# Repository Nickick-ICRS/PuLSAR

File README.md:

# PuLSAR - Probabilistic Localisation of SwArm Robots

ME4 Master's Project of Nick Hafner

Supervised by Dr Ravi Vaidyanathan

Imperial College London Department of Mechanical Engineering

## Overview of repository

This repository contains the code to localise a swarm of PuLSARs. The code is research code and no liability can be taken for any losses owing to the direct or indirect usage of this code.

The repository also contains CAD files for the Kicad PCB and Solidworks models.

## Example Usage

First follow the installation instructions below.

### Running Gazebo
(In a new terminal)
To launch a Gazebo-simulated swarm of 20 robots with the Group Motion state machine:

`$ roslaunch pulsar_gazebo multiple_robots.launch num_robots:=20 state_machine_type:=group_target`.

To launch a Gazebo-simulated swarm of 10 robots with no state machine running:

`$ roslaunch pulsar_gazebo multiple_robots.launch num_robots:=10 run_state_machine:=false`

### Running Localisation Algorithms
(With Gazebo running, in a new terminal)
To launch PSOSwarmPoseEstimator with a swarm of 20 robots:

`$ roslaunch pulsar_localisation localisation.launch num_robots:=20 localiser:=pso robot_model:=scan_matching`.

To launch AverageMCLSwarmPoseEstimator with a swarm of 10 robots and the odometry robot model:

`$ roslaunch pulsar_localisation localisation.launch num_robots:=10 localiser:=average_swarm_mcl robot_model:=odometry`.

To launch MCLSwarmPoseEstimator with a swarm of 5 robots and the scan matching robot model, debugging using Valgrind//KCacheGrind:

`$roslaunch pulsar_localisation localisation.launch num_robots:=5 localiser:=mcl robot_model:=scan_matching valgrind:=true`.

etc...

### Changing Algorithm Parameters

Edit pulsar_localisation's `localisation.launch` file. See the package README or file comments for details on what parameters do.

## Requirements

### Building

This repository used [Catkin](wiki.ros.org/catkin) to build the sub-components. This is installed along with ROS - this set of packages has been written to run with [ROS Melodic](http://wiki.ros.org/melodic/Installation) on **Ubuntu 18.04** with **Bash**. Please start by installing ROS Melodic before attempting to install any of these packages.

Create the following directory layout:
```
catkin_ws
  -> src
```

Run

`cd catkin_ws/src && catkin_init_workspace && cd .. && catkin_make` 

to generate the initial workspace. After this, clone this repository into the src folder:

`cd src && git clone <this package url>`

Install the required dependencies:

`cd PuLSAR && ./install_dependencies.sh`

Finally build the full set of packages:

`cd ../.. && catkin_make`

## Package Layout

### pulsar_cad

This package contains the CAD files needed to manufacture the PuLSAR robots. Solidworks and Kicad were used for mechanical and electrical design respectively. Kicad is free, however Solidworks will require a license to view files.

### pulsar_description

This package contains the stl meshes and urdf files required for the robot description in the ROS ecosystem. URDF has been split up into multiple files, with `urdf/pulsar.urdf.xacro` the top level URDF file.

### pulsar_gazebo

This package contains files relevant to simulating PuLSAR in the Gazebo robot simulator.

#### Launch

The launch folder contains the roslaunch files necessary to launch the simulation environment. `one_robot.launch` launches a single robot, while `multiple_robots.launch` will spawn multiple robots.

##### One Robot

This launch file spawns one pulsar robot with accompanying nodes (not localisation) in the Gazebo simulator, optionally starting the simulator. It is supposed to be called recursively from `multiple_robots.launch`, but exposes the following parameters if a user wishes to use it:

- robot_ns - The name(space) of the robot. String. Default is 'pulsar_0'.
- launch_gazebo - Whether to launch gazebo or not. Boolean. Default is true.
- start_x - The starting x position of the robot. Decimal. Default is 0.
- start_y - The starting y position of the robot. Decimal. Default is 0.
- start_yaw - The starting yaw position of the robot in radians. Decimal. Default is 0.
- start_z - The starting z height of the robot. Useful for preventing robots from clipping through the floor. Decimal. Default is 0.02.
- run_state_machine - Should the launch file spawn a state machine for the robot. Boolean. Default is true.
- state_machine_type - Which state machine should be spawned (see pulsar_state_machines). String. Default is "default". Options are:
    - "default" - Random movement state machine.
    - "group_target" - State machine which attempts to group with other robots and move towards a target point.
- map_file - Which map file to use. String. Default is "\<location of pulsar_gazebo>/maps/map.yaml".

##### Multiple Robots

This launch file spawns a swarm of pulsar robots in the Gazebo simulator, and starts the simulator. The robots are spawned in random (valid) positions. It exposes the following parameters:

- num_robots - The numberof robots to spawn. Integer. Default is 5.
- run_state_machine - Should the launch file spawn a state machine for the robot. Boolean. Default is true.
- state_machine_type - Which state machine should be spawned (see pulsar_state_machines). String. Default is "default". Options are:
    - "default" - Random movement state machine.
    - "group_target" - State machine which attempts to group with other robots and move towards a target point.
- map_file - Which map file to use. String. Default is "\<location of pulsar_gazebo>/maps/map.yaml".

### pulsar_hardware

Contains code to be compiled for the ESP-32 on the robots. Note that due to the impacts of COVID-19 on the university and project, robots could not be tested. As such this package is unfinished and has been included for completion.

### pulsar_lib

Contains custom libraries used both in simulation and in hardware such as EKF, PI controllers and Odometry.

### pulsar_localisation

Contains the developed localisation algorithms and surrounding infrastructure. It also contains the localisation launch file.

#### Launch

The launch file will run one of the localisation algorithms developed as part of this project. This should only be launched once all the robots have successfully been loaded into Gazebo. It has the following command line parameters:
- num_robots - The number of robots to localise. Should match the multiple robots launchfile parameter of the same name. Integer. Default is 1.
- valgrind - Allows the node to be launched under Valgrind for intensive debugging (e.g. function call counts). Takes precedence over gdb. Boolean. Default is false.
- gdb - Allows the node to be launched in gdb for debugging with breakpoints etc. Boolean. Default is false.
- localiser - Which localisation algorithm to use. String. Default is "mcl". Options are:
    - mcl - Runs the MCLSwarmPoseEstimator algorithm.
    - average_swarm_mcl - Runs the AverageMCLSwarmPoseEstimator algorithm. This algorithm was found to perform best.
    - pso - Runs the PSOSwarmPoseEstimator algorithm.
- robot_model - Picks which robot model to use. Note that PSO only supports scan_matching. String. Default is "odometry". Options are:
    - odometry - The odometry motion model (variant of Thrun et al.'s (2010) **odometry_motion_model**). Found to perform best.
    - scan_matching - The scan matching model.

For finer details on this launch file see the pulsar_localisation README.

### pulsar_server

Contains code to connect to robots via TCP, effectively the bridge between ROS and individual robots. Unfinished due to COVID-19, but included for completion.

### pulsar_state_machines

Contains robot state machines for swarm movement. Two state machines exist:
- Random Movement - move randomly
- Group Movement - form a group and move to a target

#### Node

The `state_machine` node runs a state machine for a given robot. It takes the following parameters:
- state_machine - Which state machine to use. String. Default is "default". Options are:
    - default - The default, random movement state machine.
    - group_target - The group motion state machine.
- robot_ns - The robot name(space). String. Default is "pulsar_0".
- update_freq - The state machine update frequency in Hz. Decimal. Default is 10.
- delay - Delay the start of state machine logic in seconds. Decimal. Default is 0.

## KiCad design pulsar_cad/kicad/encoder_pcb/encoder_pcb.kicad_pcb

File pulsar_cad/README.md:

# pulsar_cad

This package contains the CAD files needed to manufacture the PuLSAR robots.

## Kicad

The files within this folder are board layouts for the different PCBs designed using Kicad. There are three boards:
- Encoder - Contains the AS5047P magnetic encoders. 1 required per robot.
- Main Body - Contains the main components (motor driver, ESP-32, IMU etc.). 1 required per robot.
- Range Finders - Contains the VL53L0X range sensor. 3 required per robot.

## Solidworks

TODO: description of solidworks files.

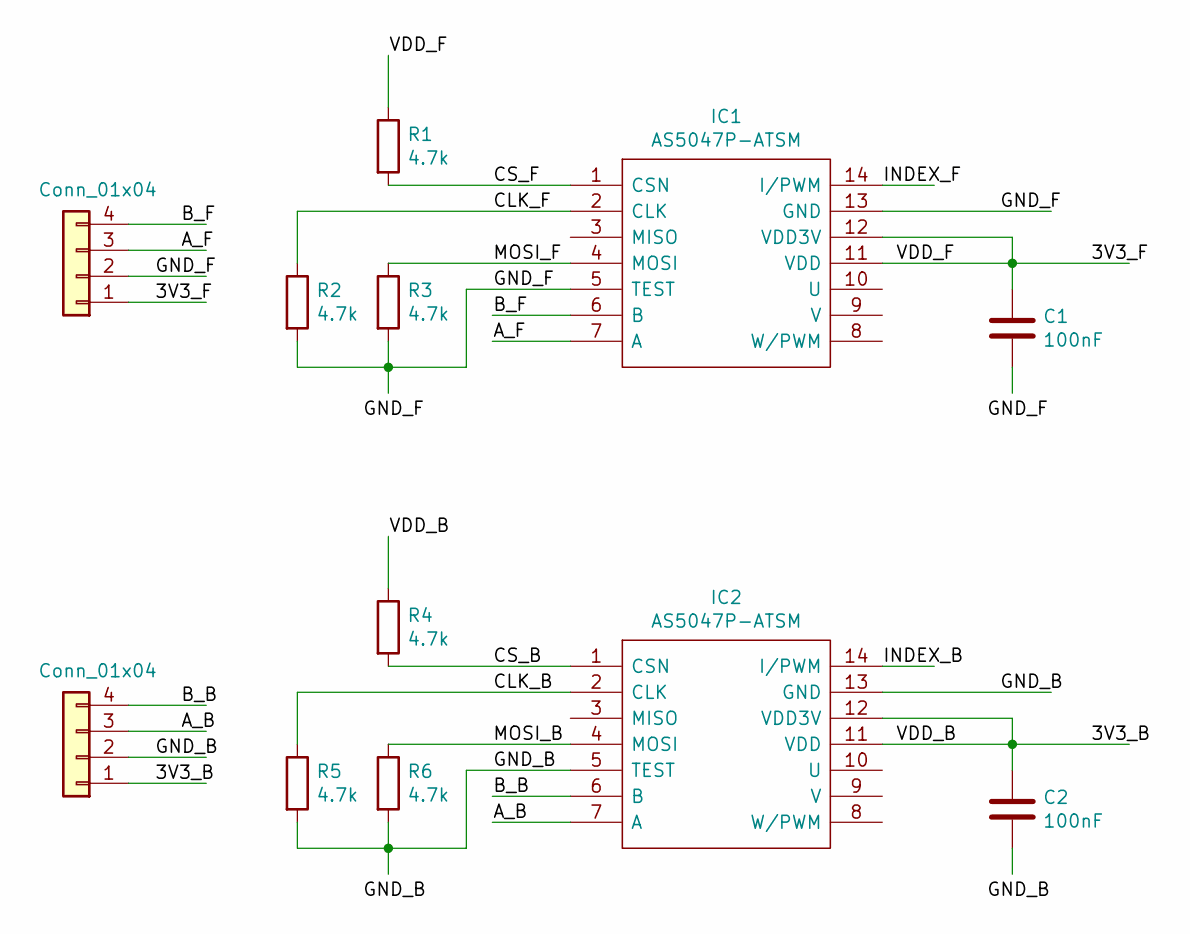
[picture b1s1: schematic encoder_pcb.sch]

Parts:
C1, C2: 100nF; C_0805_2012Metric
IC1, IC2: AS5047P-ATSM; SOP65P640X120-14N; Manufacturer_Part_Number AS5047P-ATSM
J1, J2: Conn_01x04; Connector_Pad_4x2.0x2.0mm
R1, R2, R3, R4, R5, R6: 4.7k; R_0805_2012Metric

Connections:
/3V3_B: C2.1, IC2.11 (VDD), IC2.12 (VDD3V), J2.1, R4.1
/3V3_F: C1.1, IC1.11 (VDD), IC1.12 (VDD3V), J1.1, R1.1
/A_B: IC2.7 (A), J2.3
/A_F: IC1.7 (A), J1.3
/B_B: IC2.6 (B), J2.4
/B_F: IC1.6 (B), J1.4
/CLK_B: IC2.2 (CLK), R5.1
/CLK_F: IC1.2 (CLK), R2.1
/CS_B: IC2.1 (CSN), R4.2
/CS_F: IC1.1 (CSN), R1.2
/GND_B: IC2.5 (TEST), IC2.13 (GND), J2.2, R5.2, R6.2
/GND_F: IC1.5 (TEST), IC1.13 (GND), J1.2, R2.2, R3.2
/INDEX_B: IC2.14 (I/PWM)
/INDEX_F: IC1.14 (I/PWM)
/MOSI_B: IC2.4 (MOSI), R6.1
/MOSI_F: IC1.4 (MOSI), R3.1

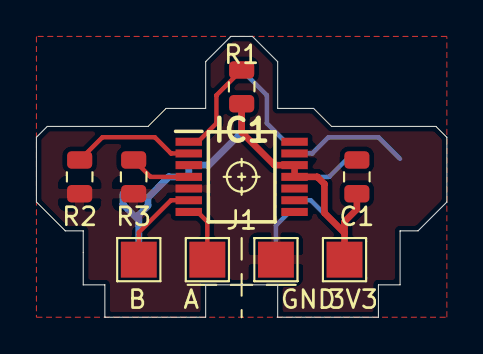
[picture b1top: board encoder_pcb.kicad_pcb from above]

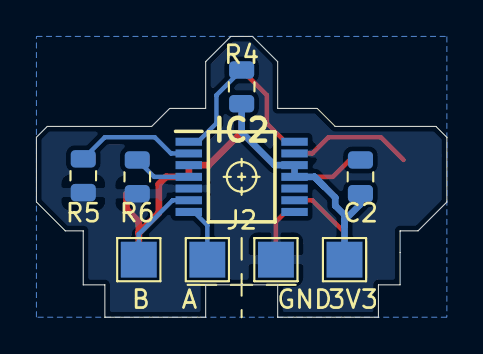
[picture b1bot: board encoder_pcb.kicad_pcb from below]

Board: 2 copper layers, 22.8 x 15.6 mm, 12 parts (6 on the bottom side), 14 nets.

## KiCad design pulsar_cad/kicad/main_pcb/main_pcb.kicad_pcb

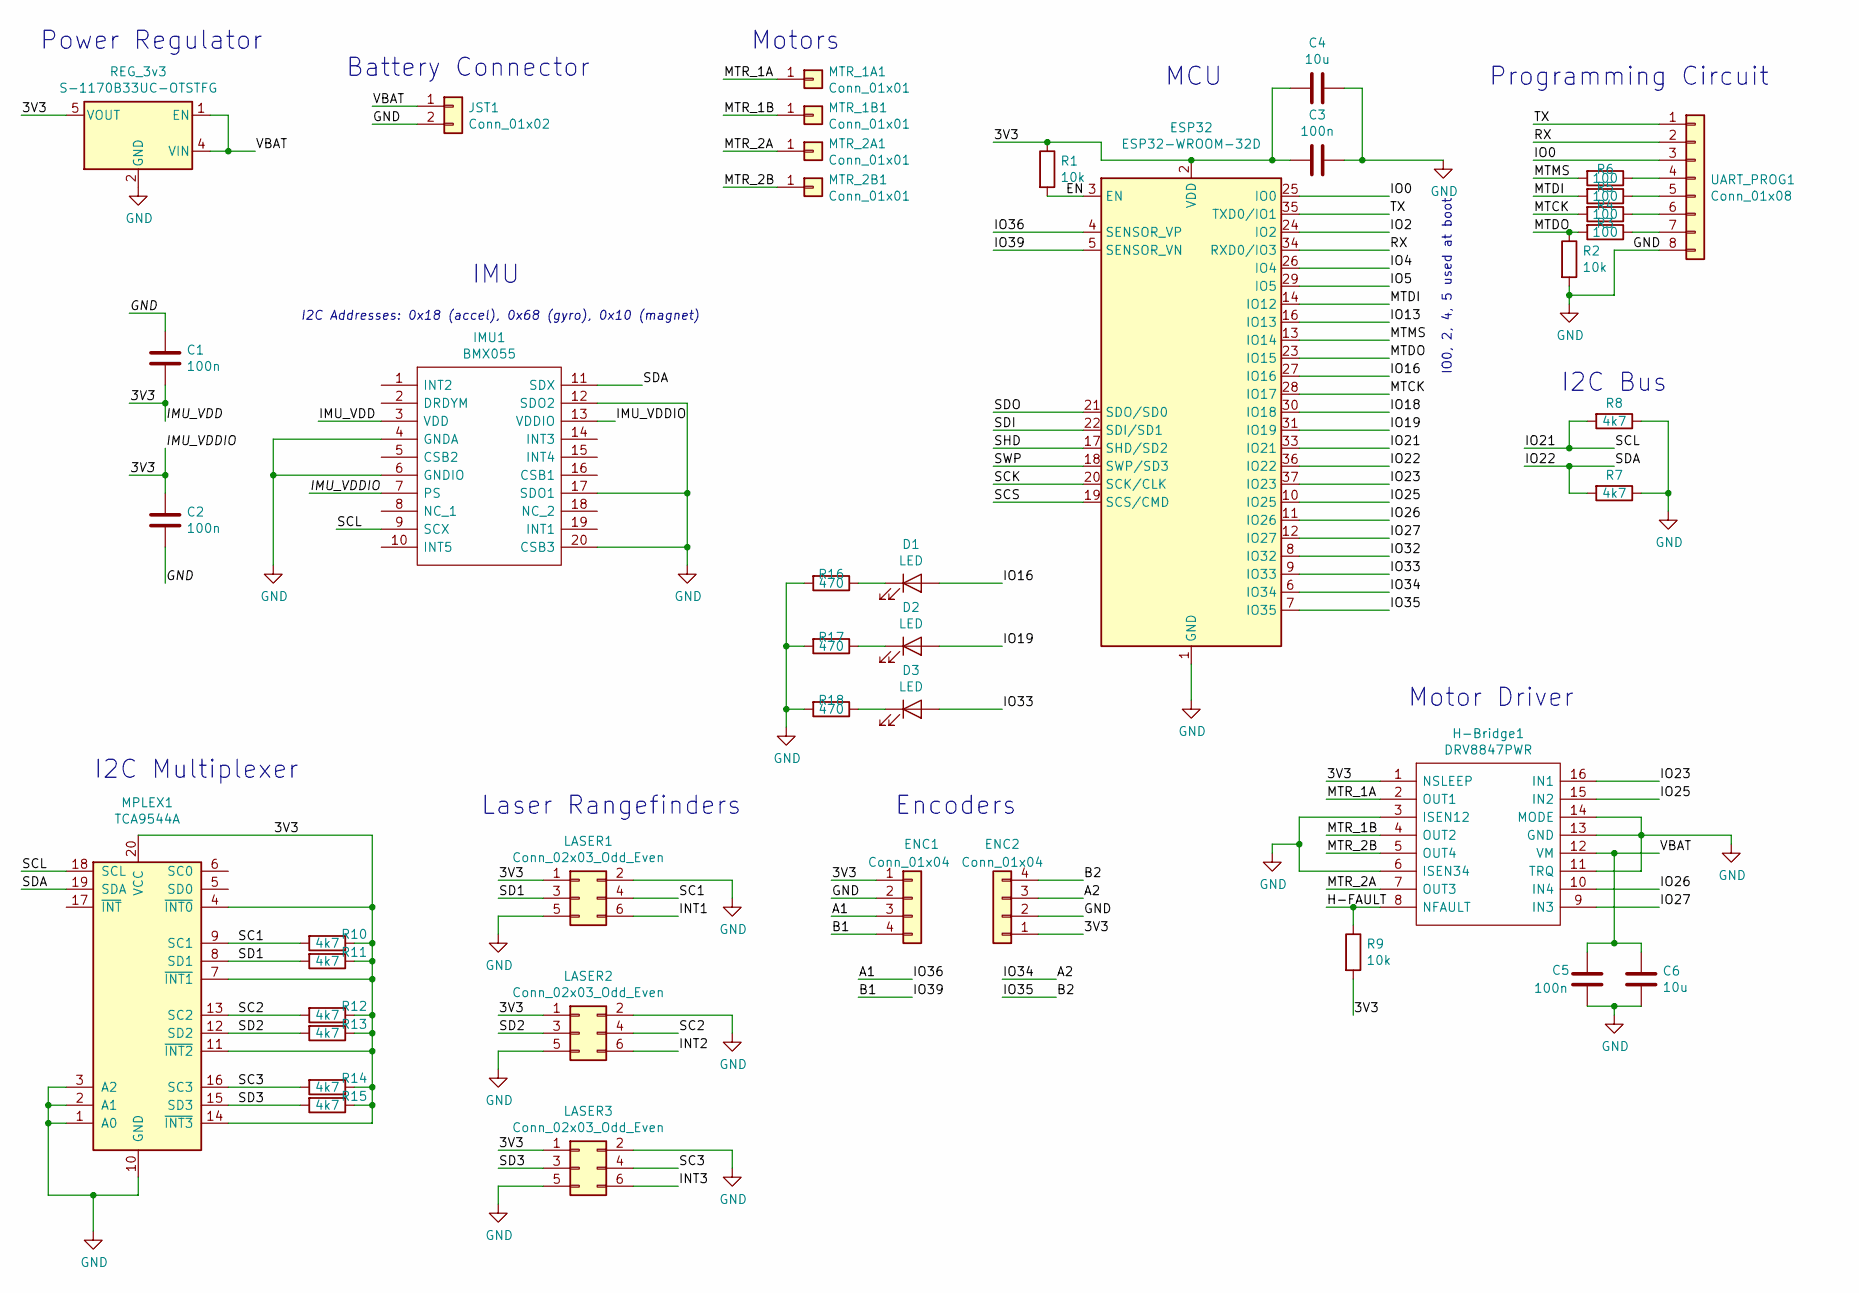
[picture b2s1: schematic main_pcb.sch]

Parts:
C1, C2, C3, C5: 100n; C_0805_2012Metric
C4, C6: 10u; C_0805_2012Metric
D1, D2, D3: LED; D_0805_2012Metric
ENC1, ENC2: Conn_01x04; Connector_Pad_4x2.0x2.0mm
ESP32: ESP32-WROOM-32D; ESP32-WROOM-32
H-Bridge1: DRV8847PWR; SOP65P640X120-16N; Manufacturer_Part_Number DRV8847PWR
IMU1: BMX055; LGA_PACKAGE_20_PINS; Manufacturer_Part_Number BMX055
JST1: Conn_01x02; JST_EH_B2B-EH-A_1x02_P2.50mm_Vertical
LASER1, LASER2, LASER3: Conn_02x03_Odd_Even; PinHeader_2x03_P2.54mm_Horizontal
MPLEX1: TCA9544A; TSSOP-20_4.4x6.5mm_P0.65mm
MTR_1A1, MTR_1B1, MTR_2A1, MTR_2B1: Conn_01x01; PinHeader_1x01_P1.00mm_Vertical
R1, R2, R9: 10k; R_0805_2012Metric
R3, R4, R5, R6: 100; R_0805_2012Metric
R7, R8, R10, R11, R12, R13, R14, R15: 4k7; R_0805_2012Metric
R16, R17, R18: 470; R_0805_2012Metric
REG_3v3: S-1170B33UC-OTSTFG; SOT-89-5
UART_PROG1: Conn_01x08; PinHeader_1x08_P2.54mm_Vertical

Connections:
/3V3: C1.2, C2.1, C3.2, C4.2, ENC1.1, ENC2.1, ESP32.2 (VDD), H-Bridge1.1 (NSLEEP), IMU1.3 (VDD), IMU1.7 (PS), IMU1.13 (VDDIO), LASER1.1, LASER2.1, LASER3.1, MPLEX1.4 (~INT0), MPLEX1.7 (~INT1), MPLEX1.11 (~INT2), MPLEX1.14 (~INT3), MPLEX1.20 (VCC), R1.1, R9.2, R10.1, R11.1, R12.1, R13.1, R14.1, R15.1, REG_3v3.5 (VOUT)
/A1: ENC1.3, ESP32.4 (SENSOR_VP)
/A2: ENC2.3, ESP32.6 (IO34)
/B1: ENC1.4, ESP32.5 (SENSOR_VN)
/B2: ENC2.4, ESP32.7 (IO35)
/EN: ESP32.3 (EN), R1.2
/H-FAULT: H-Bridge1.8 (NFAULT), R9.1
/INT1: LASER1.6
/INT2: LASER2.6
/INT3: LASER3.6
/IO0: ESP32.25 (IO0), UART_PROG1.3
/IO2: ESP32.24 (IO2)
/IO4: ESP32.26 (IO4)
/IO5: ESP32.29 (IO5)
/IO13: ESP32.16 (IO13)
/IO16: D1.2 (A), ESP32.27 (IO16)
/IO18: ESP32.30 (IO18)
/IO19: D2.2 (A), ESP32.31 (IO19)
/IO21: ESP32.33 (IO21), IMU1.9 (SCX), MPLEX1.18 (SCL), R8.2
/IO22: ESP32.36 (IO22), IMU1.11 (SDX), MPLEX1.19 (SDA), R7.2
/IO23: ESP32.37 (IO23), H-Bridge1.16 (IN1)
/IO25: ESP32.10 (IO25), H-Bridge1.15 (IN2)
/IO26: ESP32.11 (IO26), H-Bridge1.10 (IN4)
/IO27: ESP32.12 (IO27), H-Bridge1.9 (IN3)
/IO32: ESP32.8 (IO32)
/IO33: D3.2 (A), ESP32.9 (IO33)
/MTCK: ESP32.28 (IO17), R4.2
/MTDI: ESP32.14 (IO12), R5.2
/MTDO: ESP32.23 (IO15), R2.1, R3.2
/MTMS: ESP32.13 (IO14), R6.2
/MTR_1A: H-Bridge1.2 (OUT1), MTR_1A1.1
/MTR_1B: H-Bridge1.4 (OUT2), MTR_1B1.1
/MTR_2A: H-Bridge1.7 (OUT3), MTR_2A1.1
/MTR_2B: H-Bridge1.5 (OUT4), MTR_2B1.1
/RX: ESP32.34 (RXD0/IO3), UART_PROG1.2
/SC1: LASER1.4, MPLEX1.9 (SC1), R10.2
/SC2: LASER2.4, MPLEX1.13 (SC2), R12.2
/SC3: LASER3.4, MPLEX1.16 (SC3), R14.2
/SCK: ESP32.20 (SCK/CLK)
/SCS: ESP32.19 (SCS/CMD)
/SD1: LASER1.3, MPLEX1.8 (SD1), R11.2
/SD2: LASER2.3, MPLEX1.12 (SD2), R13.2
/SD3: LASER3.3, MPLEX1.15 (SD3), R15.2
/SDI: ESP32.22 (SDI/SD1)
/SDO: ESP32.21 (SDO/SD0)
/SHD: ESP32.17 (SHD/SD2)
/SWP: ESP32.18 (SWP/SD3)
/TX: ESP32.35 (TXD0/IO1), UART_PROG1.1
/VBAT: C5.1, C6.1, H-Bridge1.12 (VM), JST1.1, REG_3v3.1 (EN), REG_3v3.4 (VIN)
GND: C1.1, C2.2, C3.1, C4.1, C5.2, C6.2, ENC1.2, ENC2.2, ESP32.1 (GND), ESP32.15 (GND), ESP32.38 (GND), H-Bridge1.3 (ISEN12), H-Bridge1.6 (ISEN34), H-Bridge1.11 (TRQ), H-Bridge1.13 (GND), H-Bridge1.14 (MODE), IMU1.4 (GNDA), IMU1.6 (GNDIO), IMU1.12 (SDO2), IMU1.17 (SDO1), IMU1.20 (CSB3), JST1.2, LASER1.2, LASER1.5, LASER2.2, LASER2.5, LASER3.2, LASER3.5, MPLEX1.1 (A0), MPLEX1.2 (A1), MPLEX1.3 (A2), MPLEX1.10 (GND), R2.2, R7.1, R8.1, R16.2, R17.2, R18.2, REG_3v3.2 (GND), UART_PROG1.8
unnamed: D1.1 (K), R16.1
unnamed: D2.1 (K), R17.1
unnamed: D3.1 (K), R18.1
unnamed: R3.1, UART_PROG1.7
unnamed: R4.1, UART_PROG1.6
unnamed: R5.1, UART_PROG1.5
unnamed: R6.1, UART_PROG1.4

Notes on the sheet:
I2C Addresses: 0x18 (accel), 0x68 (gyro), 0x10 (magnet)
I2C Bus
Programming Circuit
Power Regulator
Battery Connector
Motor Driver
IMU
MCU
Encoders
IO0, 2, 4, 5 used at boot
Laser Rangefinders
I2C Multiplexer
Motors

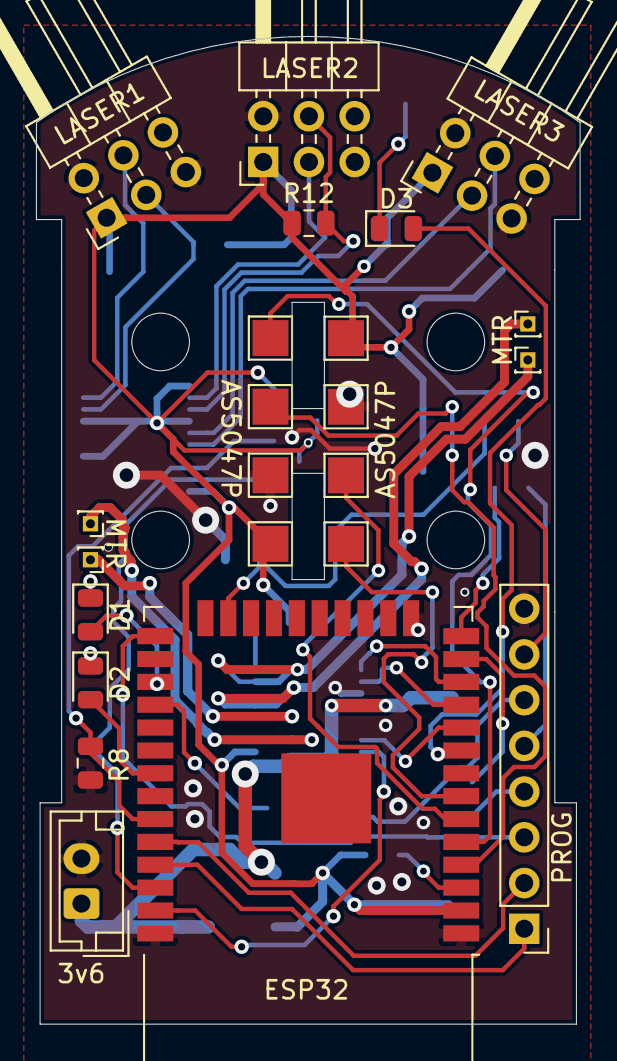
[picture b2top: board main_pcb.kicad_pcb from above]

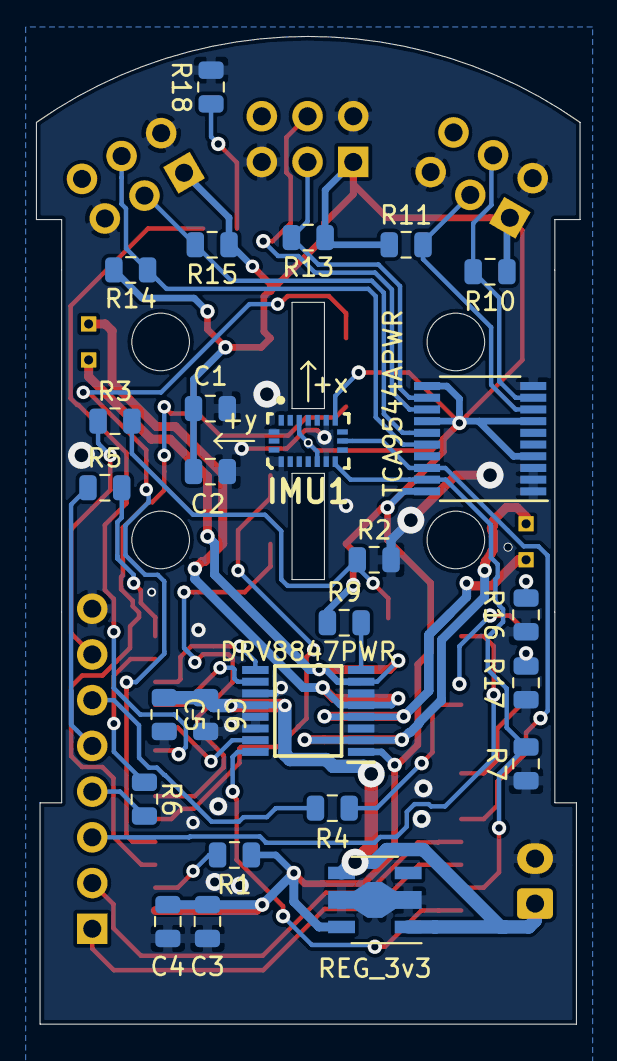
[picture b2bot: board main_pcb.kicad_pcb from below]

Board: 2 copper layers, 30.2 x 54.9 mm, 43 parts (26 on the bottom side), 42 nets.

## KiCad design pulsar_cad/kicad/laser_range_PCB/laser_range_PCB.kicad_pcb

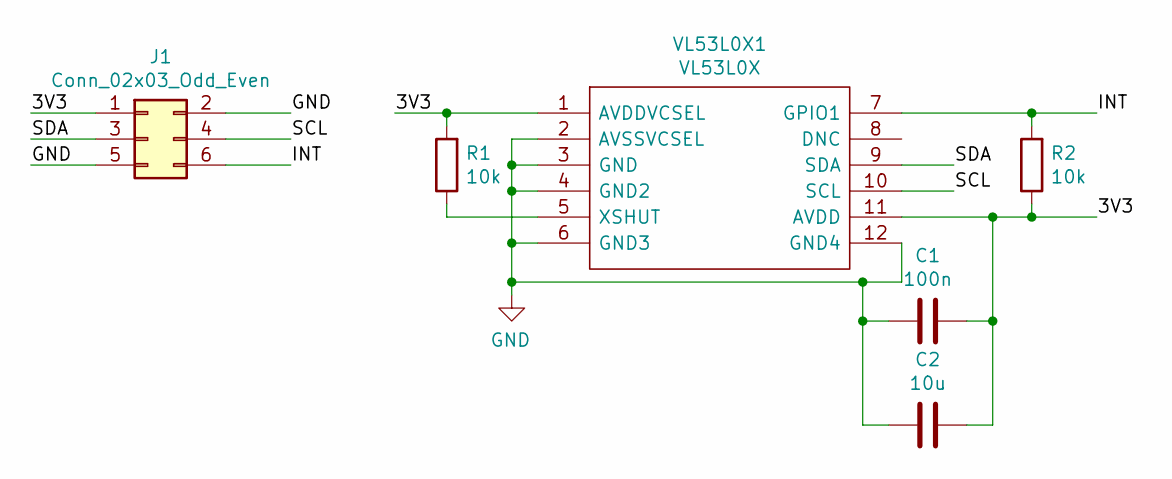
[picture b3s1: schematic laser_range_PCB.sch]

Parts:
C1: 100n; C_0805_2012Metric
C2: 10u; C_0805_2012Metric
J1: Conn_02x03_Odd_Even; PinSocket_2x03_P2.54mm_Vertical
R1, R2: 10k; R_0805_2012Metric
VL53L0X1: VL53L0X; Manufacturer_Part_Number VL53L0X

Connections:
/3V3: C1.1, C2.1, J1.1, R1.2, R2.1, VL53L0X1.1 (AVDDVCSEL), VL53L0X1.11 (AVDD)
/INT: J1.6, R2.2, VL53L0X1.7 (GPIO1)
/SCL: J1.4, VL53L0X1.10 (SCL)
/SDA: J1.3, VL53L0X1.9 (SDA)
GND: C1.2, C2.2, J1.2, J1.5, VL53L0X1.2 (AVSSVCSEL), VL53L0X1.3 (GND), VL53L0X1.4 (GND2), VL53L0X1.6 (GND3), VL53L0X1.12 (GND4)
unnamed: R1.1, VL53L0X1.5 (XSHUT)

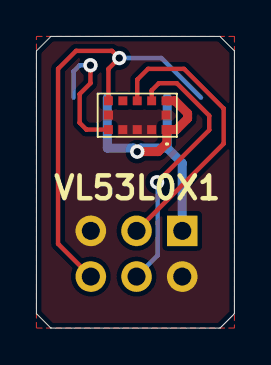
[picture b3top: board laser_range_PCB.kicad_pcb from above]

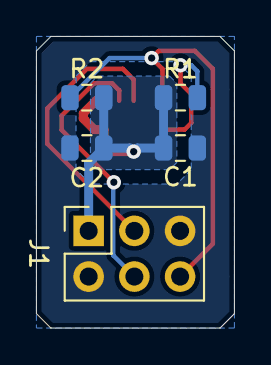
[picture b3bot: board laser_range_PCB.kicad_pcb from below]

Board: 2 copper layers, 11.0 x 16.2 mm, 6 parts (5 on the bottom side), 6 nets.

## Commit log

2019-12-26 Initial commit with a large amount of networking stuff
2020-01-14 Got chassis link loaded correctly into Gazebo, but for some reason the wheel links are missing. This does not appear to be an issue with xacro, in fact the links simply are not coming up in gazebo at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
2020-01-16 Model correctly inserted into gazebo, sensor plugins added.
2020-01-16 Started frameweork on a PuLSAR gazebo plugin to control the robots.
2020-01-19 Created kalman filter library. Successfully compiles but un-tested
2020-01-19 Added odometry library
2020-01-19 Created motor control class. Minor updates to the odometry class
2020-01-19 Moved files around slightly, successfully imported the libraries into the robot plugin
2020-01-20 Corrected submodule requirements and installation script
2020-01-23 Added reverse calculation (i.e. forward kinematics) to odometry class
2020-01-23 Full plugin update cycle is (theoretically) complete and needs testing.
2020-01-23 Added plugin to URDF and briefly checked that it runs in gazebo. Cmd_vel didn't work so some debugging needs to be done.
2020-01-24 Fixed bug with ints instead of floats in odometry
2020-01-24 Successfully got robot moving in simulation. Need to tune PI values before beginning to look at kalman filter results.
2020-02-19 Some progress being made to tuning motor controllers for the simulation - not complete yet however.
2020-02-20 Relatively tuned motor PI controller for simulation
    Kalman filter spits out NaN values so that needs to be fixed next.
2020-02-20 Fixed the Kalman filter issue with NaNs. Kalman filter needs tuning and figuring out why theta is not being used to update the x and y positions
2020-03-02 Big current hardware commit that I should have done in multiple commits quite a while ago
2020-03-05 Fixed bug with odometry, changed physics engine. Played with friction values.
2020-03-08 Implemented ROS EKF to allow algorithm to be developed and custom EKF fixed later. Fixed bug when calculating linear speeds in odometry. There is noticeable drift in simulation (which is good - that'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
2020-03-10 Adjusted one_robot.launch to allow for multiple robots to be launched in different namespaces, in different positions.
2020-03-10 Working launch file for multiple robots in the same simulation
2020-03-10 Removed print statements temporarily as will look at in the future. Fixed an issue in how friction was specified, but this has not changed the turning issue.
2020-03-21 Initial work on creating the cloud of points from robot sensors.
2020-03-21 Fixed bug causing all nodes to shut down once the last robot had been spawned
2020-03-23 Created localisation launch file, added parameters to the localisation node.
2020-03-23 Some mods to range finder coning. Updated world to have walls.
2020-03-24 Updated script to pause gazebo while robots are being spawned in and unpause once robots have all been spawned.
2020-03-24 updated cloud generator to remove old data points.
2020-03-27 Created new pose estimator classes, and rearranged layout slightly. Created parameters for pose estimator classes, next step is to fill in the algorithms.
2020-03-27 Implemented many of the Probabilistic Robotics algorithms in the SingleRobotPoseEstimator. Measurement models not implemented yet. Initial work on the map class, pose validation without considering o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
2020-03-28 Added map + server. Updated robot spawning to check map for validity and not spawn robots upon each other. Verified with 100 robots. Updated map manager checking with bugs found from spawn robot. Fil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
2020-03-28 Created RangeCloudSensorModel class, and filled in probability functions. Ray tracing not yet done in the map. I need to reformat how the sensor data is stored, as I have lost important information f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
2020-03-30 Sensor model parameters added, cloud generator now also stores the raw Range measurements. Added ray and cone casting stuff to map manager, but it isn't quite finished yet. TODO: Finish ray casting s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
2020-03-31 Code compiles and brief tests on cone tracing run without crashing. There are some logic errors which I've started diving into with gdb, but definitely still require more work.
2020-04-01 Tested cone and ray, and finally fixed issues to get them working.
2020-04-05 Created script to find range sensor intrinsic parameters and added these parameters to the launch file.
2020-04-05 Lots of bug fixes of null ptrs etc. Identified bottleneck in the range_cloud_sensor model (line 185 of single_robot_pose_estimator.cpp), which still needs fixing.
2020-04-06 Improved performance bottleneck, however the filter currently diverges. More work needed on parameters and bug checking etc. to figure out why the filter is diverging.
2020-04-07 Fixed the issue with divergence, and added in a section to keep the pose estimates of the filter within the map. However, we experience a large amount of drift, perhaps the range sensor model isn't w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
2020-04-08 Still trying to fix the range sensor model. There seems to be an issue with the generation of ideal_z (the ray casted sensor reading) - however ray casting is working fine in isolation.
2020-04-10 Fixed issues with quaternion mathematics. Made some adjustments to the range sensor - we now have an issue that occaisionally a *huge* weight is produced - I am unsure why and will continue to invest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
2020-04-11 Somehow the obscene weights have been removed. Still have an issue with filter drift however.
2020-04-11 Implemented dbscan clustering to remove outlier pose estimates and improve the overall robot pose estimation. This works really well! (But does not help with the drift.)
2020-04-11 MCL seems to work well when I stop EKF from publishing the odometry transform and have MCL run the localisation alone (still with EKF data however). Of course it runs too slow and discontinuous, but 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
2020-04-11 Fixed issued with coordinate transforms. The drift appears to have returned however - I still think this is because the range sensor model is poorly tuned.
2020-04-12 Made a simple state machine to aid in data capture for the range sensor parameter learning.
2020-04-12 Adjusted state machine and learning parameter model. Relearned sensor intrinsic parameters - they are now much closer to the expected values.
2020-04-14 Fixed issue with ray casting ray casting in the wrong direction
2020-04-15 Playing with the amount of data processed per update and parameters has resulted in a much cleaner and faster filter. However, running the filter faster (e.g. 20Hz) results in explosive theta changes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
2020-04-16 Adding in a form of minimum movement before update worked quite well. Removing wfast and wslow also greatly improved the filter, and a faster 'make_pose_valid' function has been written. Fixed an iss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
2020-04-17 Fixed loss of poses. Cause was a division by zero creating an infinite/nan weight.
2020-04-17 Created a plotting script to plot robot movements in order to compare the effectiveness of different methods of localisation.
2020-04-17 Updated code to now run the full localisation with multiple robots within the swarm, and estimate the swarm position based upon these measurements.
2020-04-18 Threaded update code. Removed unnecessary debug statements. Removed unused parts of the cloud generator. Fixed a crashing bug gue to dereferencing a null iterator.
2020-04-19 Made a cleaner state machine class inheritance system, and placed within a new package. Made a group state machine that attempts to move robots of the swarm to a requested position in the map. Needs 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
2020-04-20 Make a 'perfect' localisation script to test the state machine with. After some minor fixed the state machine is working well. Also fixed a bug with transform calculations.
2020-04-21 Fixed issue when starting odometry was not 0,0,0
2020-04-21 Adjusted pose estimator layout to make the swarm class abstract and inheritable.
2020-04-21 Code refactor to enable better class inheritance for robot pose estimators etc. Started some initial framework for an alternative swarm pose estimator.
2020-04-22 Made SingleRobotPoseEstimator abstract - MCLSingleRobotPoseEstimator is now what SingleRobotPoseEstimator was.
2020-04-23 Cleaned up unused functions. Fixed map manager robot maps and added debug visualisations. Fixed bug in single robot pose estimator causing Xt to lose all members. Began work on the second localisatio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
2020-04-24 Created new localisation algorithm. Needs fine tuning, as currently nearby robots coverge upone each other.
2020-04-25 Added clustering to the second filter - it diverges incredibly quickly. Perhaps an alternative sensor/robot model needs to be tried.
2020-04-26 Created new robot model to try scan matching in addition to odometry model info, along with inheritance restructuring. Needs further testing however.
2020-04-26 Lots of playing with PCL, e.g. ICP etc. Updating the weigh pose and using normal odometry was okish - I got a much faster runtime than the range sensor model version. I think if I can get the matchin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
2020-04-27 Got scan matching working to a reasonable level and speed - however, it can lose the robot quite easily when the robot turns. Further work needs to be done to attempt to ensure pose continuity.
2020-04-27 Attempt to reduce points in map cloud so it's only the edges. Needs confirmation.
2020-04-30 Map cloud size reduction worked after minor change. Looking at the scan matching model, it seems that we need to take higher weighting of the actual motion model to prevent sudden teleportation.
2020-04-30 Scan matching works quite well, given the lack of data points. Still have issues with the group mcl method causing robots to converge upon themselves.
2020-05-26 Big commit including PSO I forgot to include earlier, as well as many changes made for testing etc...
2020-06-01 Final changes for testing
2020-06-01 Cad file temporary files to make file structure
2020-06-01 pulsar_gazebo package documentation
2020-06-01 formatting
2020-06-01 pulsar_description documentation
2020-06-01 pulsar_cad documentation
2020-06-01 pulsar_hardware documentation.
2020-06-01 pulsar_lib documentation.
2020-06-01 pulsar_server documentation
2020-06-01 pulsar_state_machine documentation
2020-06-03 pulsar_localisation documentation
2020-06-03 Final documentation commit ?
2020-06-03 formatiing
2020-06-09 Solidworks files
2020-06-09 PCB Files
